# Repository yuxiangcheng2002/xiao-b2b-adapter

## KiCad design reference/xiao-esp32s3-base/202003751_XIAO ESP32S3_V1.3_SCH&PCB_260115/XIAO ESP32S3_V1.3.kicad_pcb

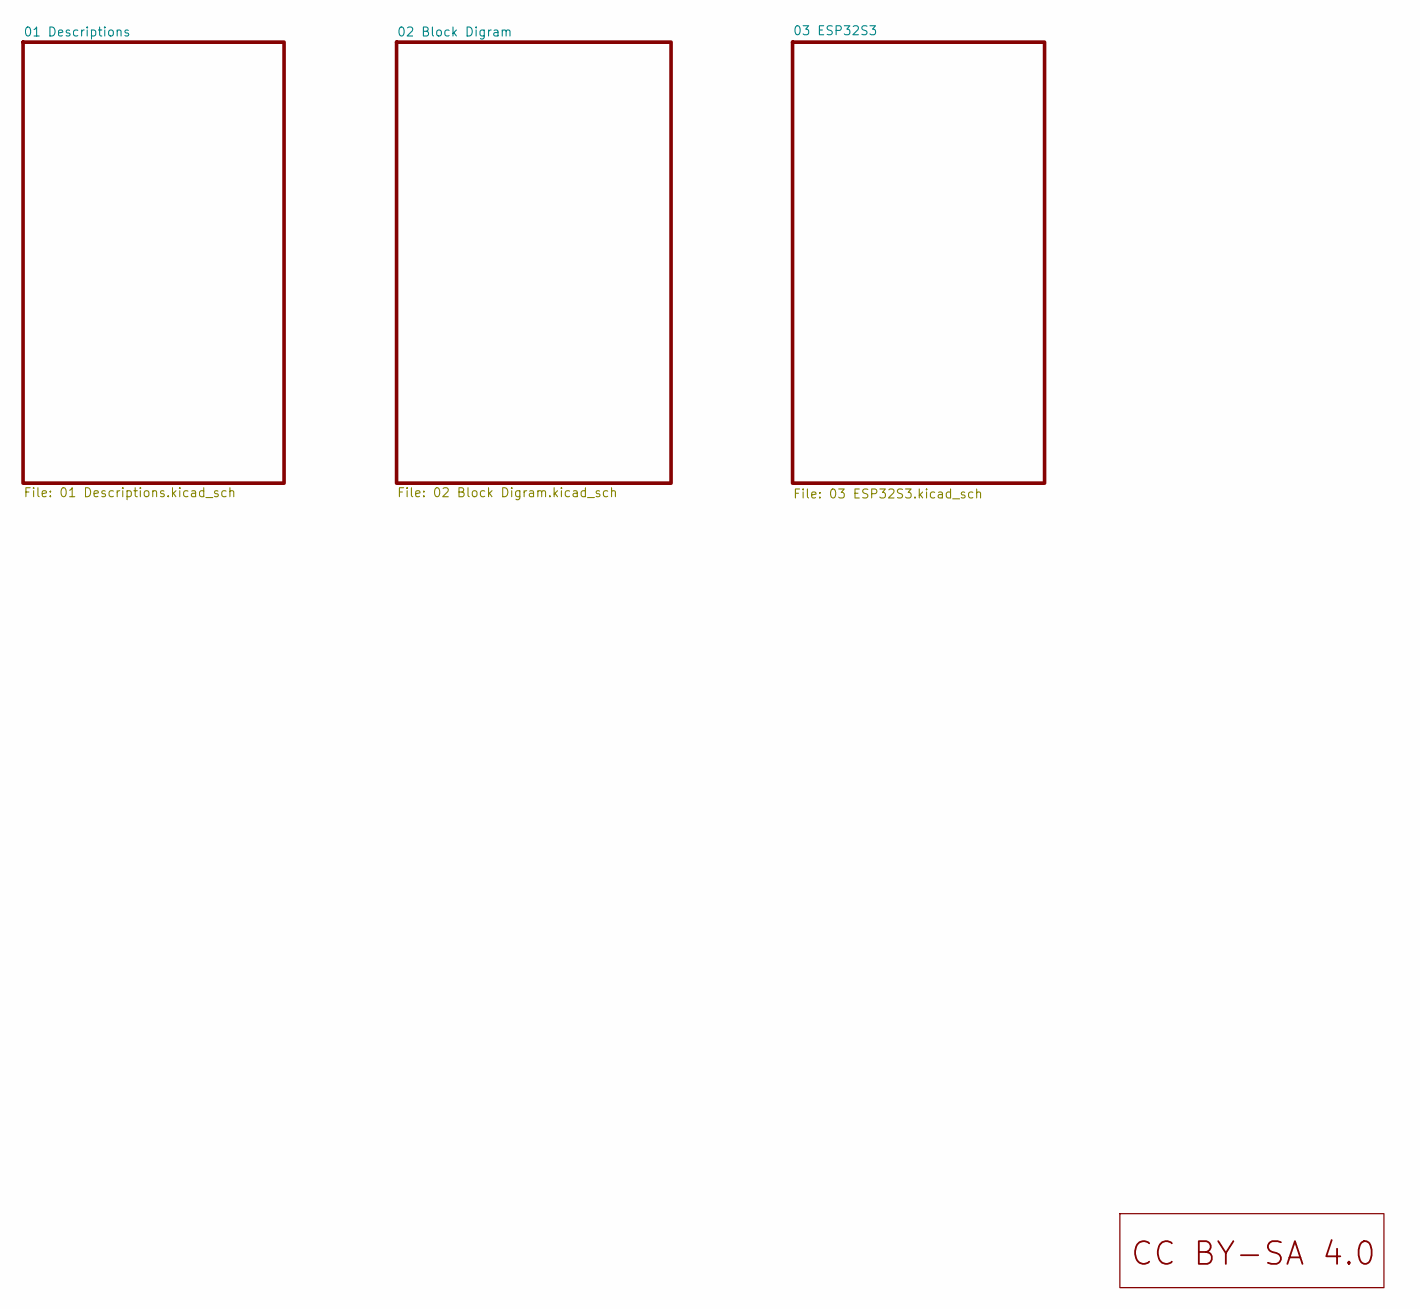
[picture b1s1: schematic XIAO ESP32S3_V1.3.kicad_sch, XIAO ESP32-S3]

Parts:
U2: LOGO_CC_BY-SA_4.0

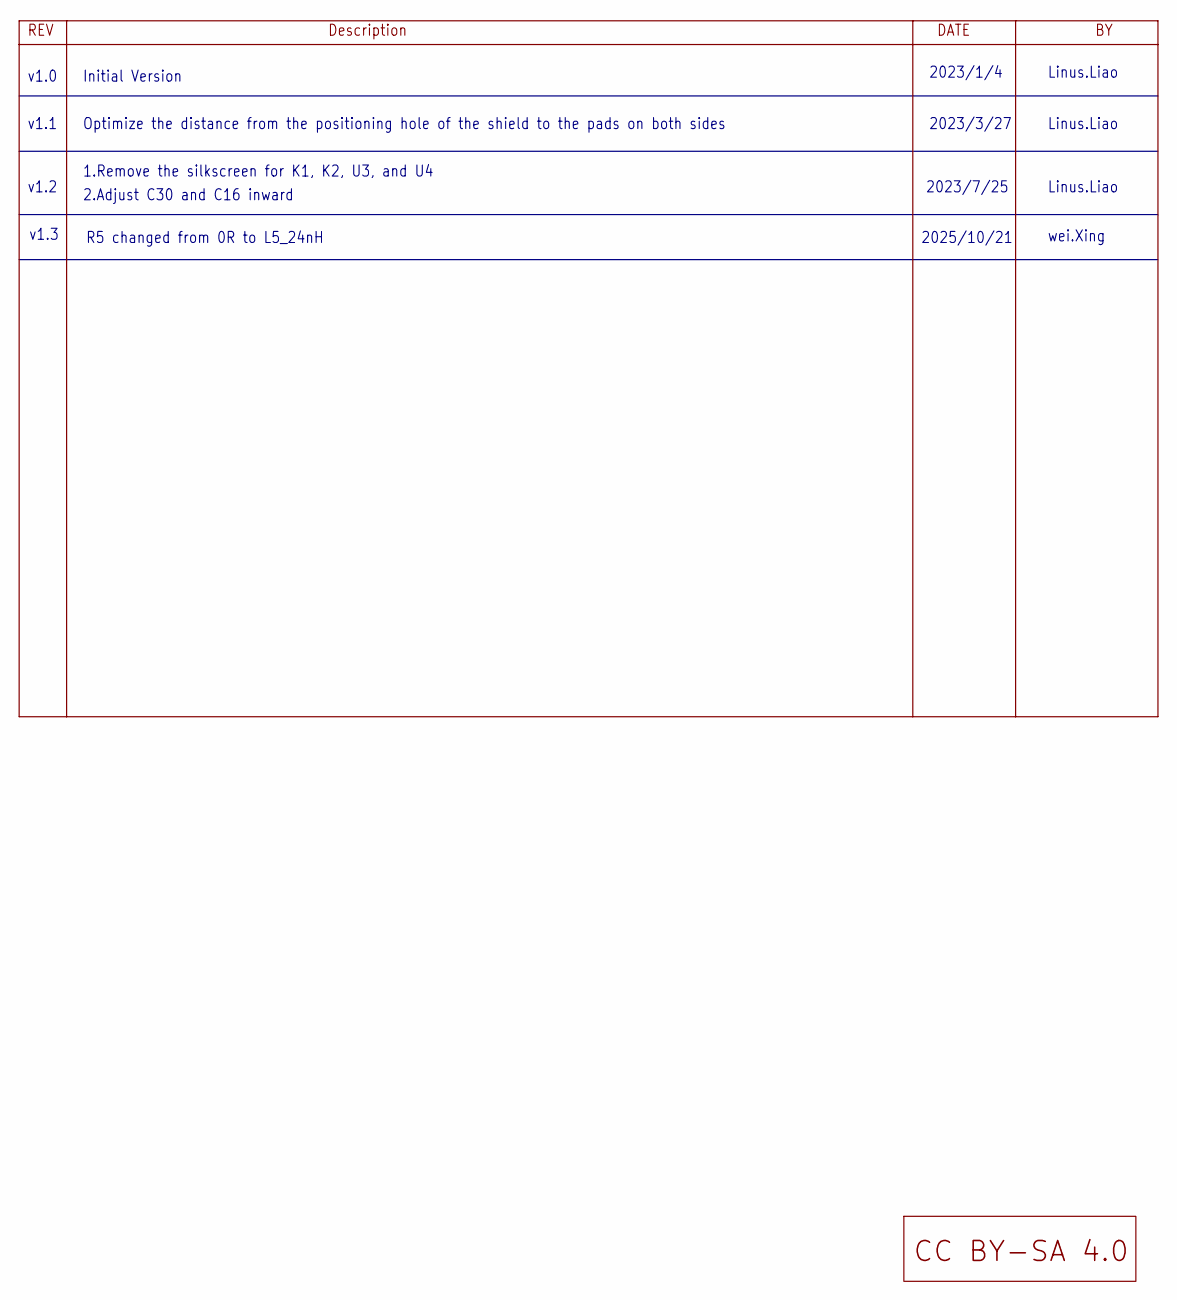
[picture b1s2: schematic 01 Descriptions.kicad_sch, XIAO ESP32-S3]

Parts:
U6: LOGO_CC_BY-SA_4.0

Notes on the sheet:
2023/7/25
R5 changed from 0R to L5_24nH
Linus.Liao
Optimize the distance from the positioning hole of the shield to the pads on both sides
2023/1/4
Initial Version
v1.1
v1.0
2025/10/21
v1.3
1.Remove the silkscreen for K1, K2, U3, and U4
wei.Xing
v1.2
2.Adjust C30 and C16 inward
2023/3/27

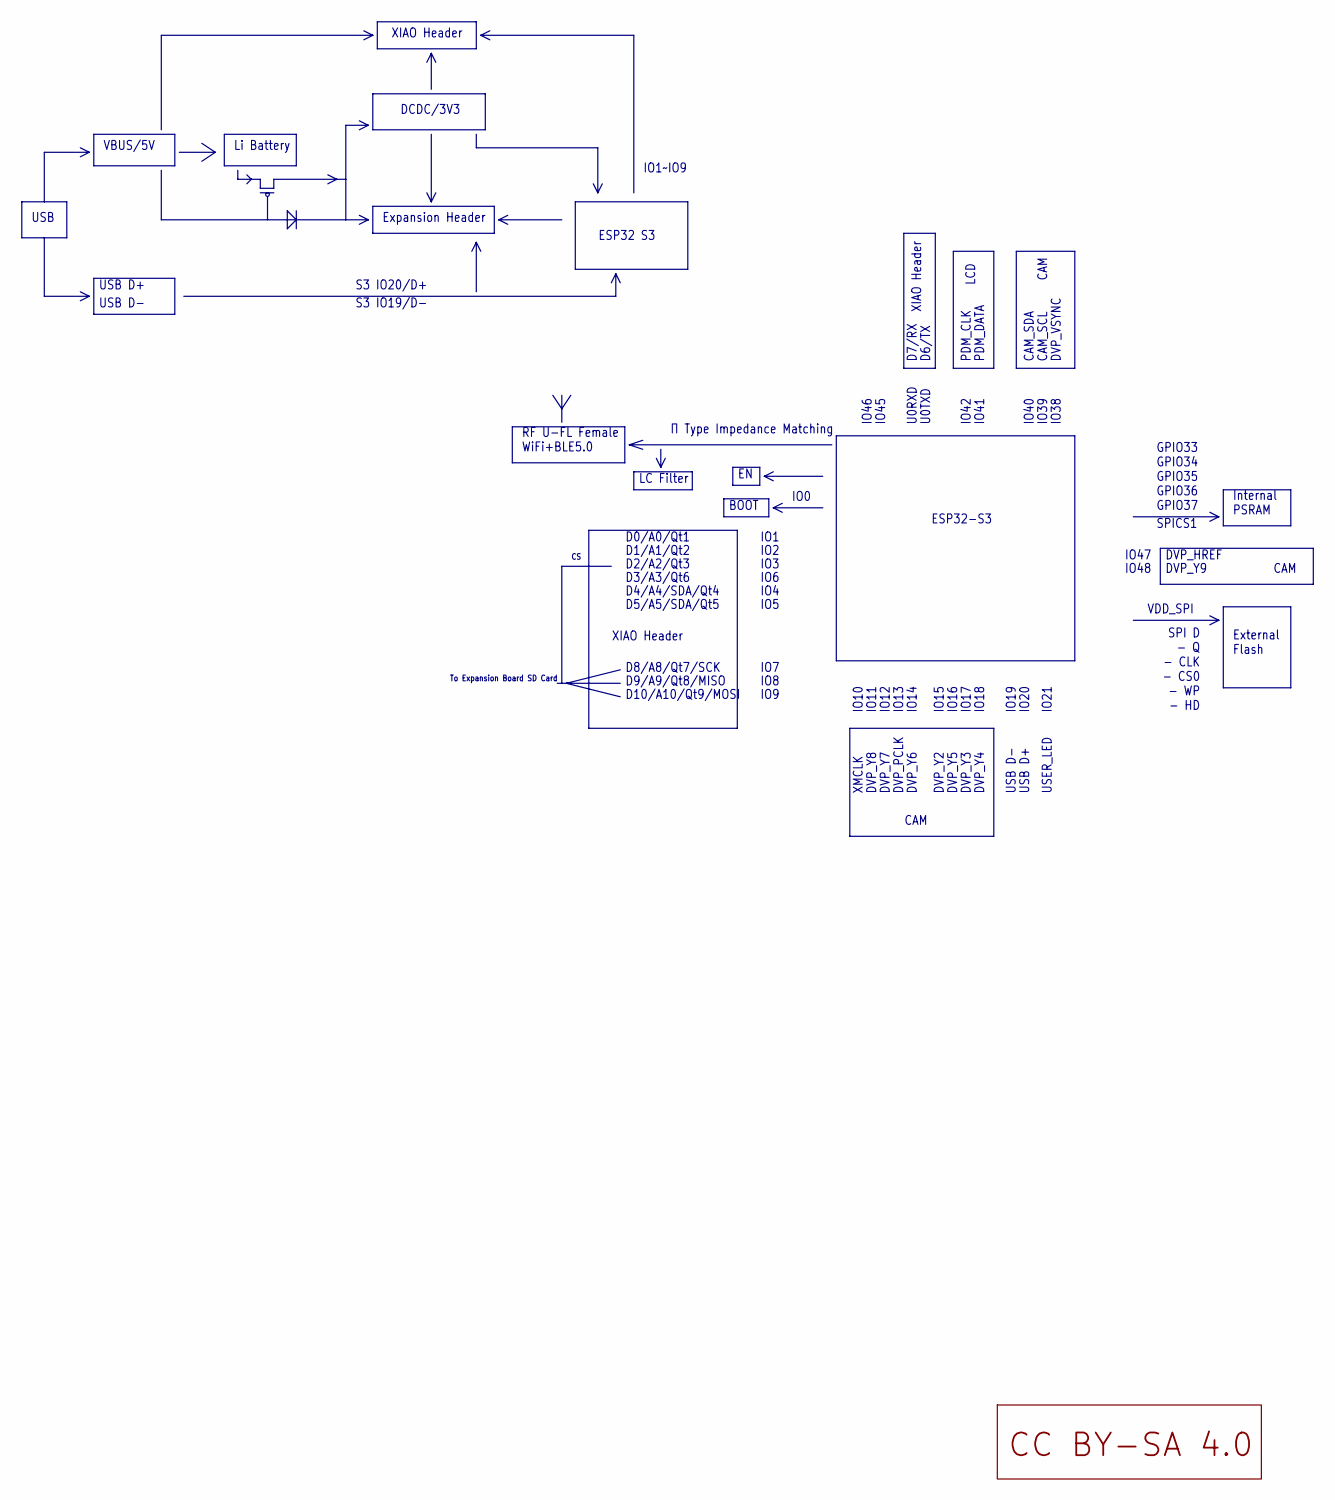
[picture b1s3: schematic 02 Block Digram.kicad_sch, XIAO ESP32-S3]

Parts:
U9: LOGO_CC_BY-SA_4.0

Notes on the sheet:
IO39
BOOT
D4/A4/SDA/Qt4
IO1
IO15
PDM_CLK
ESP32-S3
IO13
PDM_DATA
DVP_HREF
D5/A5/SDA/Qt5
CAM
USB D-
IO48
IO21
IO46
IO8
D10/A10/Qt9/MOSI
IO45
IO1~IO9
To Expansion Board SD Card
VBUS/5V
DVP_Y7
LCD
IO14
IO12
IO2
CAM_SCL
USB D+
Li Battery
GPIO33 GPIO34 GPIO35 GPIO36 GPIO37
XIAO Header
DVP_Y6
IO6
IO38
DVP_Y2
DVP_Y9
D0/A0/Qt1
D3/A3/Qt6
D1/A1/Qt2

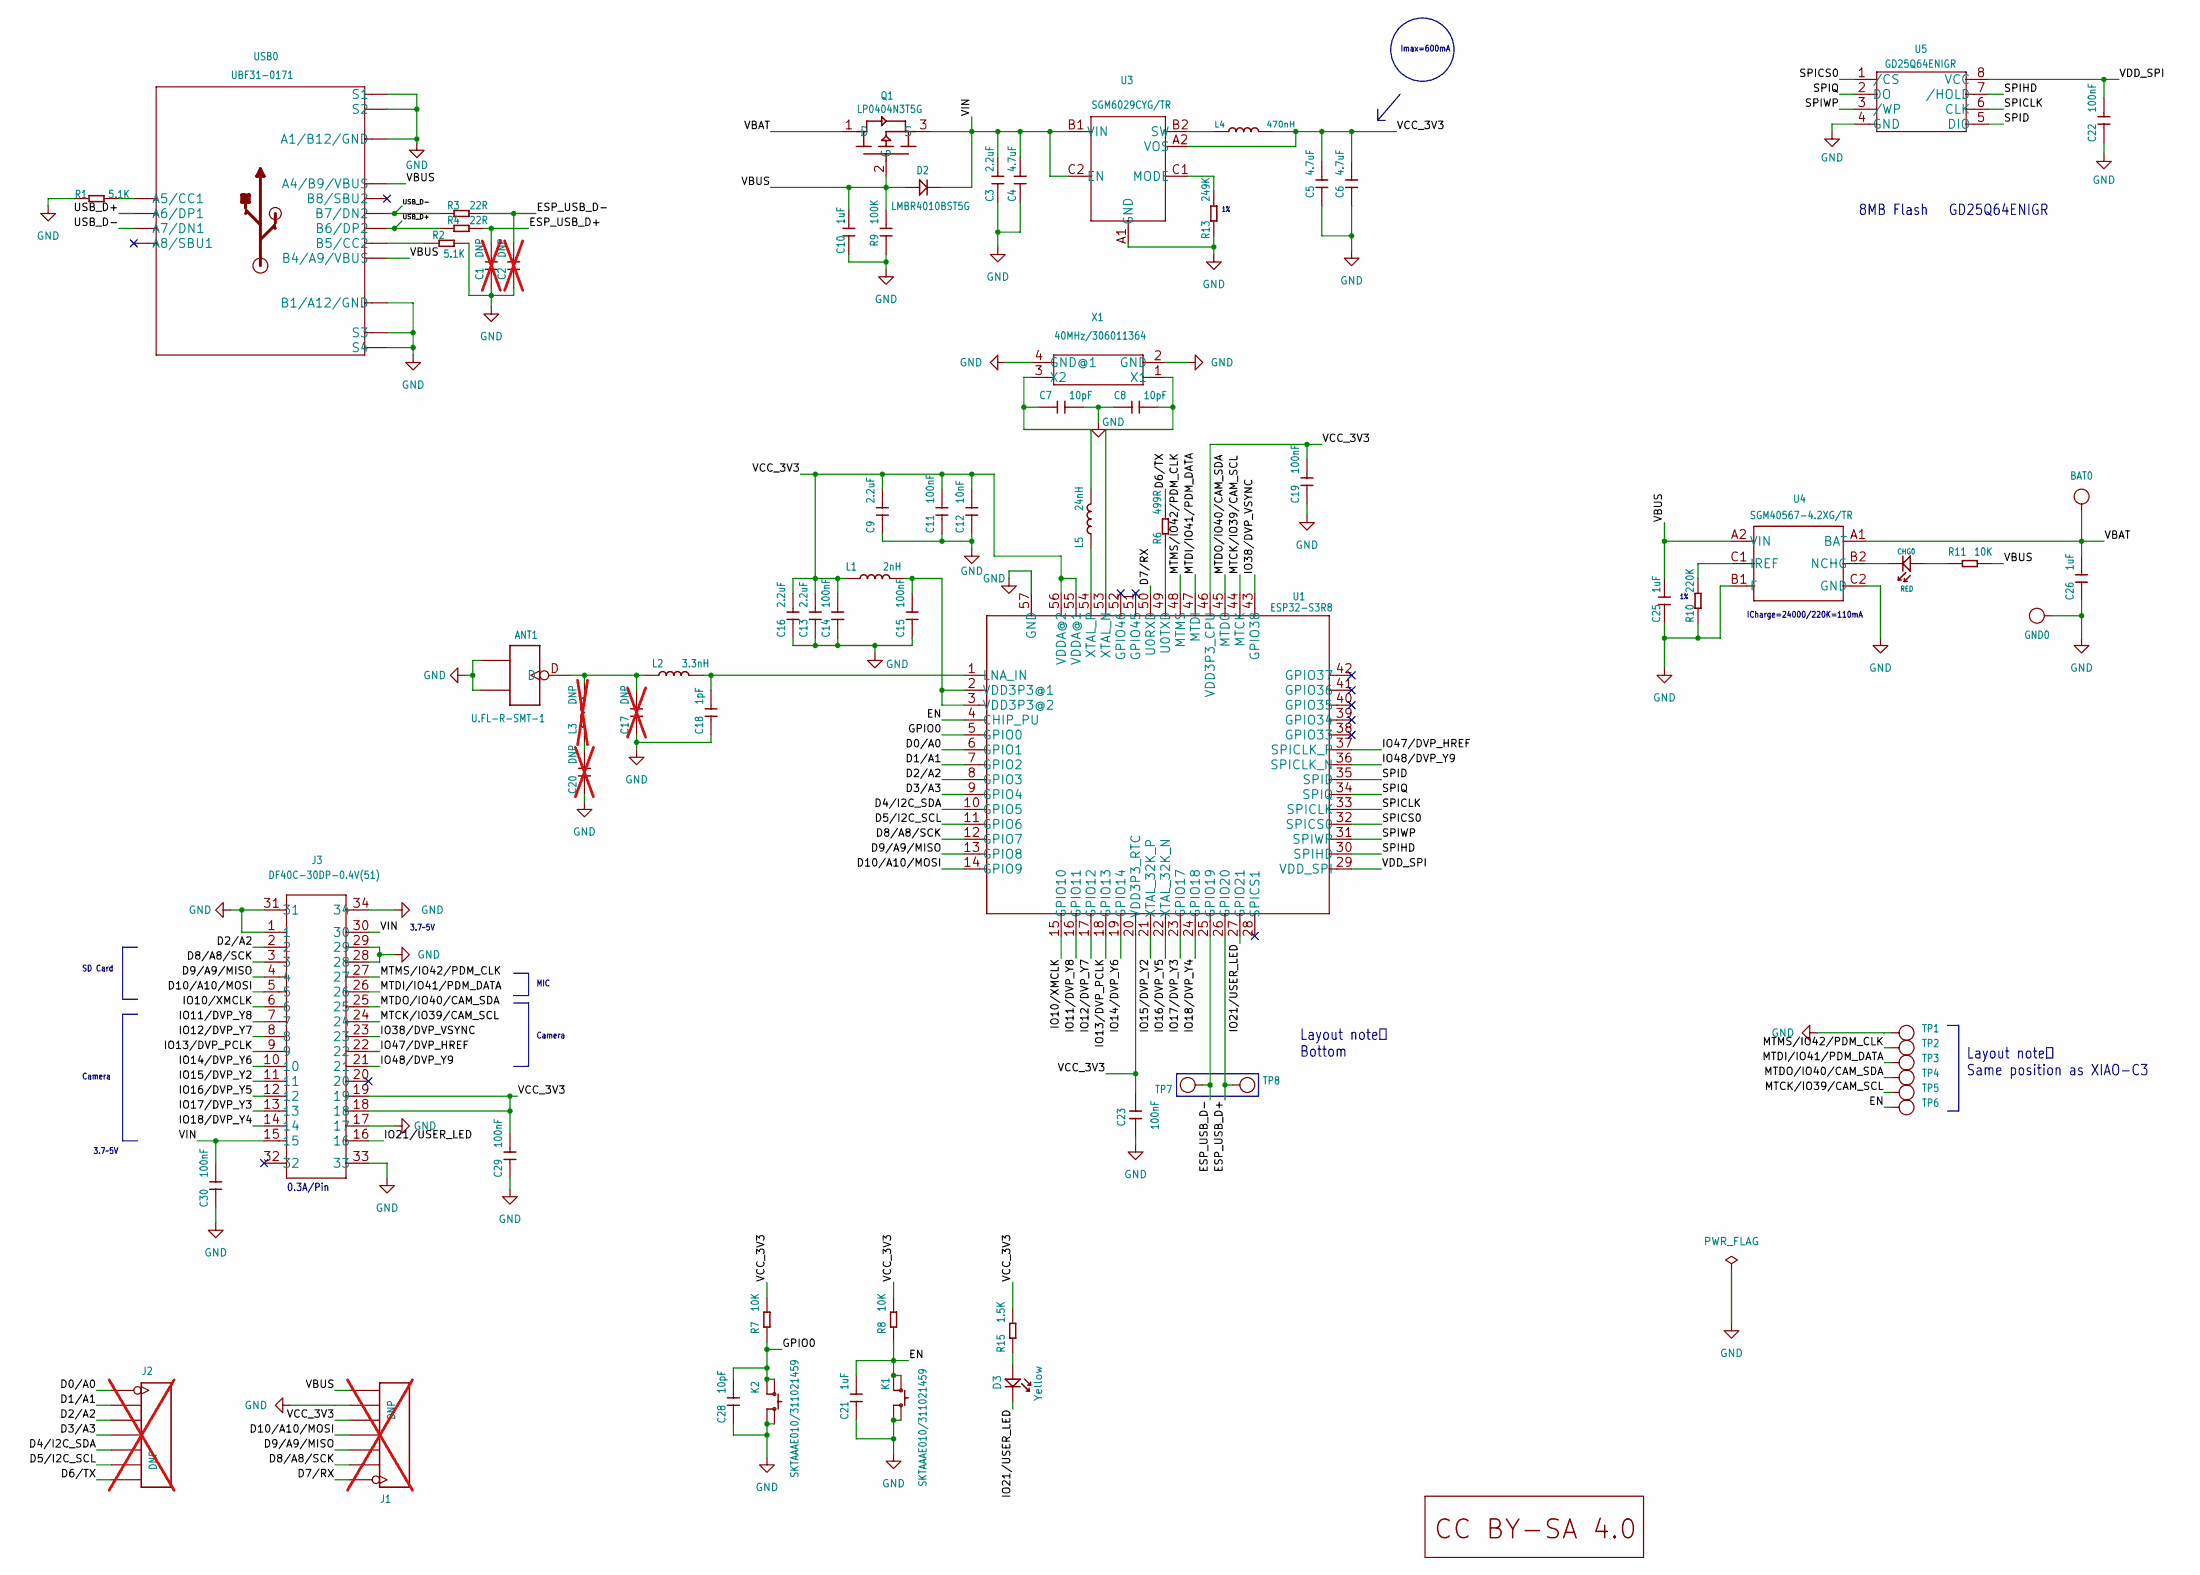
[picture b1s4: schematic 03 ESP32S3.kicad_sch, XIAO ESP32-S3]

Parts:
ANT1: U.FL-R-SMT-1; U-FL3P-SMD-2.6X2.6X1.0MM
BAT0: VBAT; TP-80X40MIL
C1, C2, C17, C20: DNP; C0201; not fitted
C3, C9, C13, C16: 2.2uF; C0201
C4, C5, C6: 4.7uF; C0201
C7, C8, C28: 10pF; C0201
C10, C21, C25, C26: 1uF; C0201
C11, C14, C15, C19, C22, C23, C29, C30: 100nF; C0201
C12: 10nF; C0201
C18: 1pF; C0201
CHG0: RED; LED-0402
D2: LMBR4010BST5G; DFN1006-2L
D3: Yellow; LED-0402
GND0: GND; TP-80X40MIL
J1, J2: DNP; H7-HALF-HOLE-2.54; not fitted
J3: DF40C-30DP-0.4V(51); BTB30-0.4-7.52X2.97X1.14
K1, K2: SKTAAAE010/311021459; SW4-SMD-2.8-2.6X1.6X0.53MM
L1: 2nH; L0201
L2: 3.3nH; L0201
L3: DNP; L0201; not fitted
L4: 470nH; L0603
L5: 24nH; L0201
Q1: LP0404N3T5G; PMOS_1.0_0.6_0.35MM
R1, R2: 5.1K; R0201
R3, R4: 22R; R0201
R6: 499R; R0201
R7, R8, R11: 10K; R0201
R9: 100K; C0201
R10: 220K; R0201
R13: 249K; R0201
R15: 1.5K; R0201
TP1, TP2, TP3, TP4, TP5, TP6, TP7, TP8: TEST-POINT'4545'; TP-D45MIL
U1: ESP32-S3R8; QFN56G-0.4-7X7MM
U3: SGM6029CYG/TR; BGA6-0.35-0.745X10.95X0.4MM
U4: SGM40567-4.2XG/TR; WLCSP-0.4-0.92X1.16X0.4MM
U5: GD25Q64ENIGR; USON8-0.8-4X3MM
U8: LOGO_CC_BY-SA_4.0
USB0: UBF31-0171; USB2.0-TYPE-C
X1: 40MHz/306011364; X4-SMD-1.6X1.2X0.35MM

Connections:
D0/A0: J2.1, J2.13 (1), U1.6 (GPIO1)
D1/A1: J2.2, J2.14 (2), U1.7 (GPIO2)
D2/A2: J2.3, J2.15 (3), J3.2, U1.8 (GPIO3)
D3/A3: J2.4, J2.16 (4), U1.9 (GPIO4)
D4/I2C_SDA: J2.5, J2.17 (5), U1.10 (GPIO5)
D5/I2C_SCL: J2.6, J2.18 (6), U1.11 (GPIO6)
D6/TX: J2.7, J2.19 (7), R6.2
D7/RX: J1.1, J1.13 (1), U1.50 (U0RXD)
D8/A8/SCK: J1.2, J1.14 (2), J3.3, U1.12 (GPIO7)
D9/A9/MISO: J1.3, J1.15 (3), J3.4, U1.13 (GPIO8)
D10/A10/MOSI: J1.4, J1.16 (4), J3.5, U1.14 (GPIO9)
EN: C21.2, K1.1 (A0), K1.3 (A1), R8.1, TP6.T, U1.4 (CHIP_PU)
ESP_USB_D+: C1.2, R4.2, TP8.T, U1.26 (GPIO20)
ESP_USB_D-: C2.2, R3.2, TP7.T, U1.25 (GPIO19)
GND: ANT1.GND1, ANT1.GND2, C1.1, C2.1, C3.2, C4.2, C5.1, C6.1, C7.2, C8.1, C9.1, C10.2, C11.1, C12.1, C13.1, C14.1, C15.1, C16.1, C17.1, C18.1, C19.1, C20.1, C21.1, C22.1, C23.2, C25.2, C26.2, C28.1, C29.1, C30.1, GND0.1, J1.6, J1.18 (6), J3.1, J3.17, J3.28, J3.29, J3.31, J3.33, J3.34, K1.2 (B0), K1.4 (B1), K2.2 (B0), K2.4 (B1), R1.1, R2.2, R9.1, R10.1, R13.1, TP1.T, U1.57 (GND), U3.A1 (GND), U4.B1 (F), U4.C2 (GND), U5.4 (GND), USB0.A1_B12 (A1/B12/GND), USB0.B1_A12 (B1/A12/GND), USB0.S1, USB0.S2, USB0.S3, USB0.S4, USB0.S5 (S1), USB0.S6 (S2), X1.2 (GND), X1.4 (GND@1)
GND5: L4.1, U3.B2 (SW)
GND6: R13.2, U3.C1 (MODE)
GPIO0: C28.2, K2.1 (A0), K2.3 (A1), R7.1, U1.5 (GPIO0)
IO10/XMCLK: J3.6, U1.15 (GPIO10)
IO11/DVP_Y8: J3.7, U1.16 (GPIO11)
IO12/DVP_Y7: J3.8, U1.17 (GPIO12)
IO13/DVP_PCLK: J3.9, U1.18 (GPIO13)
IO14/DVP_Y6: J3.10, U1.19 (GPIO14)
IO15/DVP_Y2: J3.11, U1.21 (XTAL_32K_P)
IO16/DVP_Y5: J3.12, U1.22 (XTAL_32K_N)
IO17/DVP_Y3: J3.13, U1.23 (GPIO17)
IO18/DVP_Y4: J3.14, U1.24 (GPIO18)
IO21/USER_LED: D3.-, J3.16, U1.27 (GPIO21)
IO38/DVP_VSYNC: J3.23, U1.43 (GPIO38)
IO47/DVP_HREF: J3.22, U1.37 (SPICLK_P)
IO48/DVP_Y9: J3.21, U1.36 (SPICLK_N)
MTCK/IO39/CAM_SCL: J3.24, TP5.T, U1.44 (MTCK)
MTDI/IO41/PDM_DATA: J3.26, TP3.T, U1.47 (MTDI)
MTDO/IO40/CAM_SDA: J3.25, TP4.T, U1.45 (MTDO)
MTMS/IO42/PDM_CLK: J3.27, TP2.T, U1.48 (MTMS)
unnamed: L5.1, U1.54 (XTAL_P)
unnamed: C7.1, L5.2, X1.3 (X2)
unnamed: C8.2, U1.53 (XTAL_N), X1.1 (X1)
unnamed: ANT1.D, C17.2, L2.1, L3.2
unnamed: R2.1, USB0.B5 (B5/CC2)
unnamed: C15.2, L1.2, U1.2 (VDD3P3@1), U1.3 (VDD3P3@2)
unnamed: R1.2, USB0.A5 (A5/CC1)
unnamed: C18.2, L2.2, U1.1 (LNA_IN)
unnamed: CHG0.-, U4.B2 (NCHG)
unnamed: R6.1, U1.49 (U0TXD)
unnamed: R10.2, U4.C1 (IREF)
unnamed: CHG0.+, R11.2
unnamed: D3.+, R15.1
unnamed: C20.2, L3.1
SPICLK: U1.33 (SPICLK), U5.6 (CLK)
SPICS0: U1.32 (SPICS0), U5.1 (/CS)
SPID: U1.35 (SPID), U5.5 (DIO)
SPIHD: U1.30 (SPIHD), U5.7 (/HOLD)
SPIQ: U1.34 (SPIQ), U5.2 (DO)
SPIWP: U1.31 (SPIWP), U5.3 (/WP)
USB_D+: R4.1, USB0.A6 (A6/DP1), USB0.B6 (B6/DP2)
USB_D-: R3.1, USB0.A7 (A7/DN1), USB0.B7 (B7/DN2)
VBAT: BAT0.1, C26.1, Q1.1 (D), U4.A1 (BAT)
VBUS: C10.1, C25.1, D2.+, J1.7, J1.19 (7), Q1.2 (G), R9.2, R11.1, U4.A2 (VIN), USB0.A4_B9 (A4/B9/VBUS), USB0.B4_A9 (B4/A9/VBUS)
VCC_3V3: C5.2, C6.2, C9.2, C11.2, C12.2, C13.2, C14.2, C16.2, C19.2, C23.1, C29.2, J1.5, J1.17 (5), J3.18, J3.19, L1.1, L4.2, R7.2, R8.2, R15.2, U1.20 (VDD3P3_RTC), U1.46 (VDD3P3_CPU), U1.55 (VDDA@1), U1.56 (VDDA@2), U3.A2 (VOS)
VDD_SPI: C22.2, U1.29 (VDD_SPI), U5.8 (VCC)
VIN: C3.1, C4.1, C30.2, D2.-, J3.15, J3.30, Q1.3 (S), U3.B1 (VIN), U3.C2 (EN)

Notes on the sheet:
Layout note： Same position as XIAO-C3
Camera
SD Card
0.3A/Pin
Layout note： Bottom
3.7~5V
MIC
ICharge=24000/220K=110mA
Imax=600mA
8MB Flash GD25Q64ENIGR

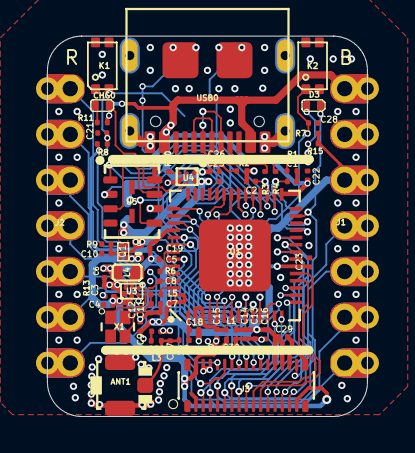
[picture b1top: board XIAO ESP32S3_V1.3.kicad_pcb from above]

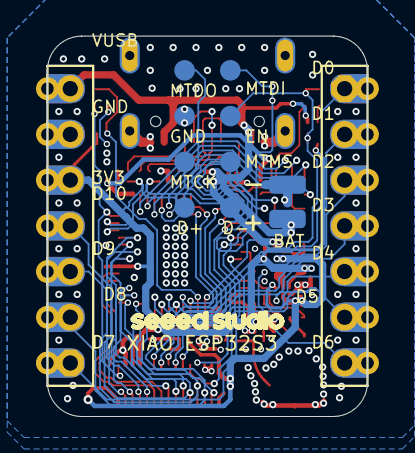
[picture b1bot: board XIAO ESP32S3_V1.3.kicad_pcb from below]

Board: 2 copper layers, 17.8 x 21.1 mm, 72 parts (11 on the bottom side), 62 nets.

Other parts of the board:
U$7: LOGO-SEEED-NEW-0.94X8.4MM

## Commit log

2026-02-21 Initial: FPC connector reference for XIAO ESP32S3 B2B adapter
2026-02-21 Add KiCad footprints + Seeed reference designs
    - FH12-30S-0.5SH footprint (KiCad official library)
    - DF40C-30DP-0.4V(51) footprint (extracted from Seeed XIAO ESP32S3 PCB)
    - XIAO ESP32S3 V1.3 schematic + PCB (KiCad, from Seeed)
    - XIAO ESP32S3 Plus V1.1 schematic + PCB (KiCad, from Seeed)
    - XIAO Plus Base V1.0 schematic + PCB + PDF (has B2B pinout)
    - XIAO ESP32S3 Sense 3D model + STEP file
